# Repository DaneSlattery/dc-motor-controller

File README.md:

# dc-motor-controller
A dc motor controller using mbed

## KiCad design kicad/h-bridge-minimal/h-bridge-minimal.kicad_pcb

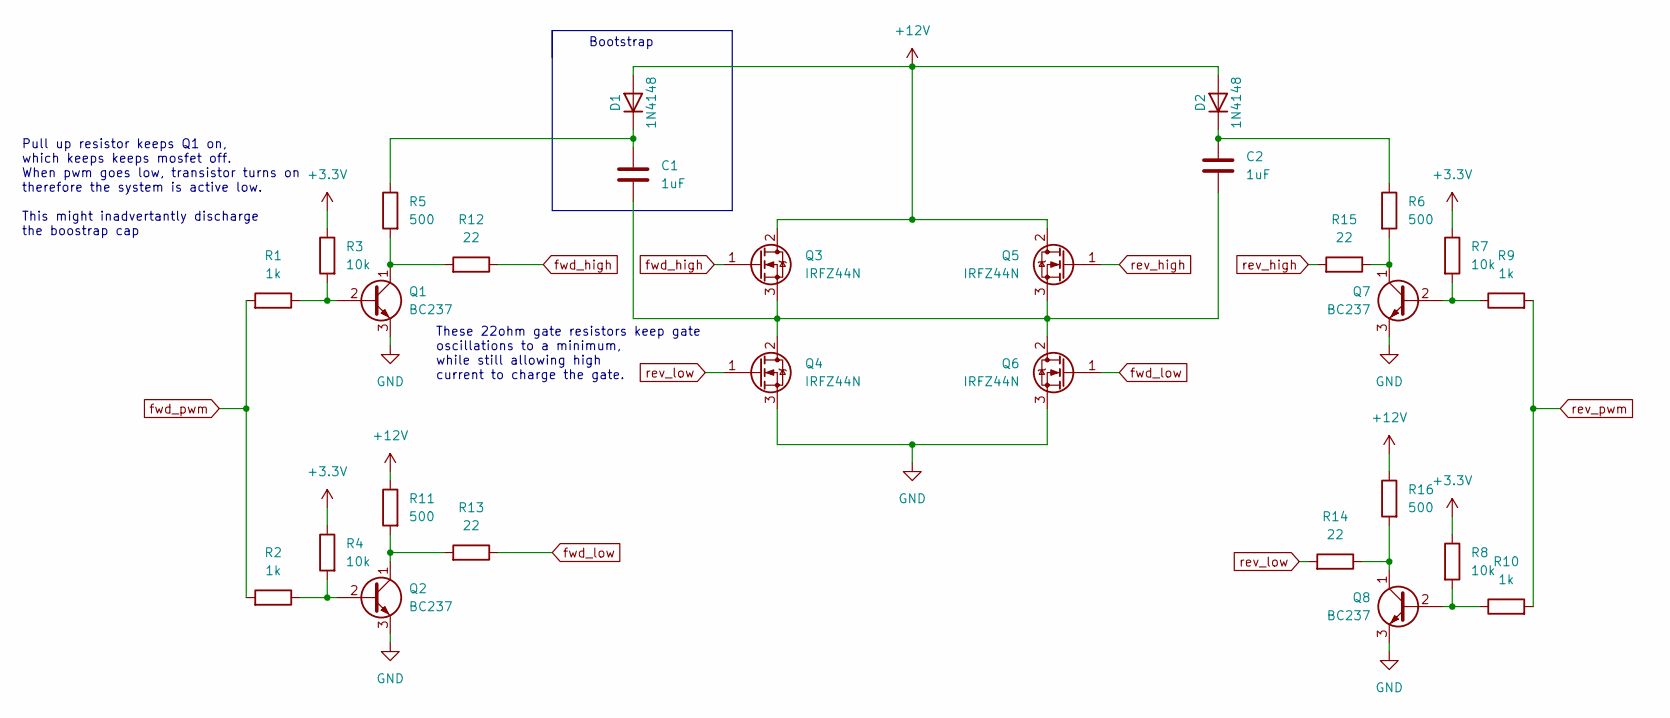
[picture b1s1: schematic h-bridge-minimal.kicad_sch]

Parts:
C1, C2: 1uF; C_Rect_L7.2mm_W3.0mm_P5.00mm_FKS2_FKP2_MKS2_MKP2
D1, D2: 1N4148; D_DO-35_SOD27_P7.62mm_Horizontal
Q1, Q2, Q7, Q8: BC237; TO-92_Inline_Wide
Q3, Q4, Q5, Q6: IRFZ44N; TO-220-3_Vertical
R1, R2, R9, R10: 1k; R_Axial_DIN0207_L6.3mm_D2.5mm_P10.16mm_Horizontal
R3, R4, R7, R8: 10k; R_Axial_DIN0207_L6.3mm_D2.5mm_P10.16mm_Horizontal
R5, R6, R11, R16: 500; R_Axial_DIN0207_L6.3mm_D2.5mm_P10.16mm_Horizontal
R12, R13, R14, R15: 22; R_Axial_DIN0207_L6.3mm_D2.5mm_P10.16mm_Horizontal

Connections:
+3.3V: R3.1, R4.1, R7.1, R8.1
+12V: D1.2 (A), D2.2 (A), Q3.2 (D), Q5.2 (D), R11.1, R16.1
GND: Q1.3 (E), Q2.3 (E), Q4.3 (S), Q6.3 (S), Q7.3 (E), Q8.3 (E)
unnamed: C1.1, D1.1 (K), R5.1
unnamed: C1.2, C2.2, Q3.3 (S), Q4.2 (D), Q5.3 (S), Q6.2 (D)
unnamed: C2.1, D2.1 (K), R6.1
unnamed: Q1.1 (C), R5.2, R12.2
unnamed: Q1.2 (B), R1.1, R3.2
unnamed: Q2.1 (C), R11.2, R13.2
unnamed: Q2.2 (B), R2.1, R4.2
unnamed: Q7.1 (C), R6.2, R15.1
unnamed: Q7.2 (B), R7.2, R9.1
unnamed: Q8.1 (C), R14.1, R16.2
unnamed: Q8.2 (B), R8.2, R10.1
fwd_high: Q3.1 (G), R12.1
fwd_low: Q6.1 (G), R13.1
fwd_pwm: R1.2, R2.2
rev_high: Q5.1 (G), R15.2
rev_low: Q4.1 (G), R14.2
rev_pwm: R9.2, R10.2

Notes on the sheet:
Bootstrap
These 22ohm gate resistors keep gate oscillations to a minimum, while still allowing high current to charge the gate.
Pull up resistor keeps Q1 on, which keeps keeps mosfet off. When pwm goes low, transistor turns on therefore the system is active low. This might inadvertantly discharge the boostrap cap

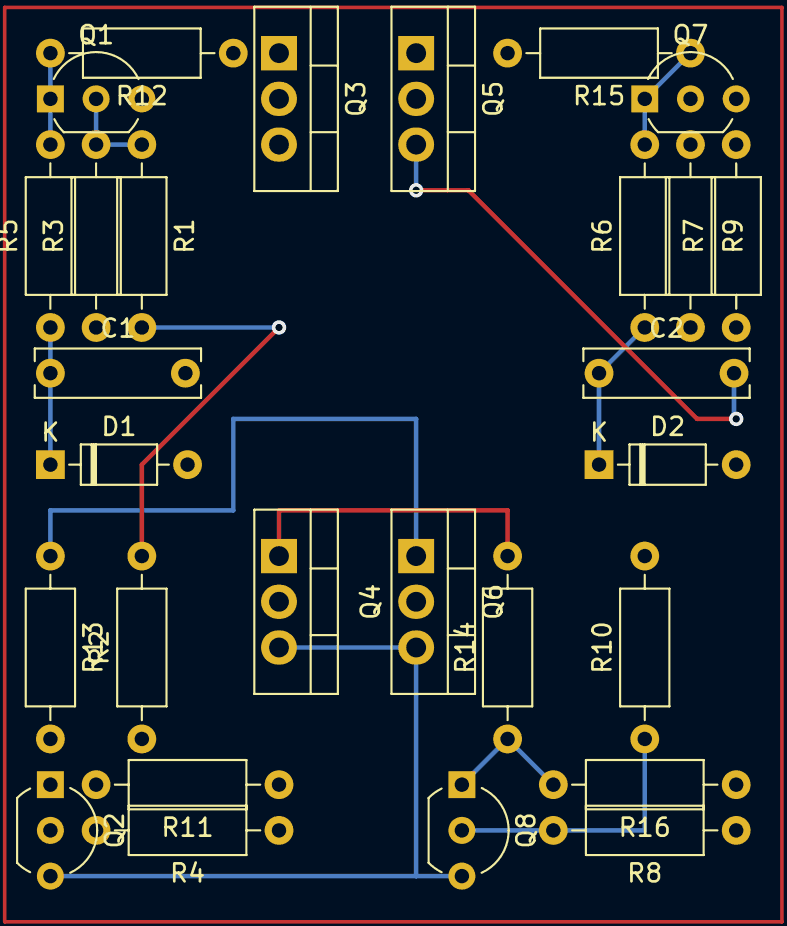
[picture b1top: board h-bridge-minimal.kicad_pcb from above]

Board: 2 copper layers, 28 parts (0 on the bottom side), 20 nets.

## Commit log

2022-07-07 Add kicad, spice and working src
2022-07-31 Added SerialPlot class for plotting variables
2022-11-16 Add PID lib
2023-02-06 Added idf
2023-02-07 Converted optical encoder
2023-02-07 Add fix for optical init
2023-02-09 Calculate RPM
2023-03-24 Add stepper motor control
